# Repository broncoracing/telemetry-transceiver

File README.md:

# telemetry transceiver
Bronco racing BR24 telemetry transceiver.

Based on an XBee Pro 900HP transceiver, and an STM32F412 microcontroller with two CAN transceivers.

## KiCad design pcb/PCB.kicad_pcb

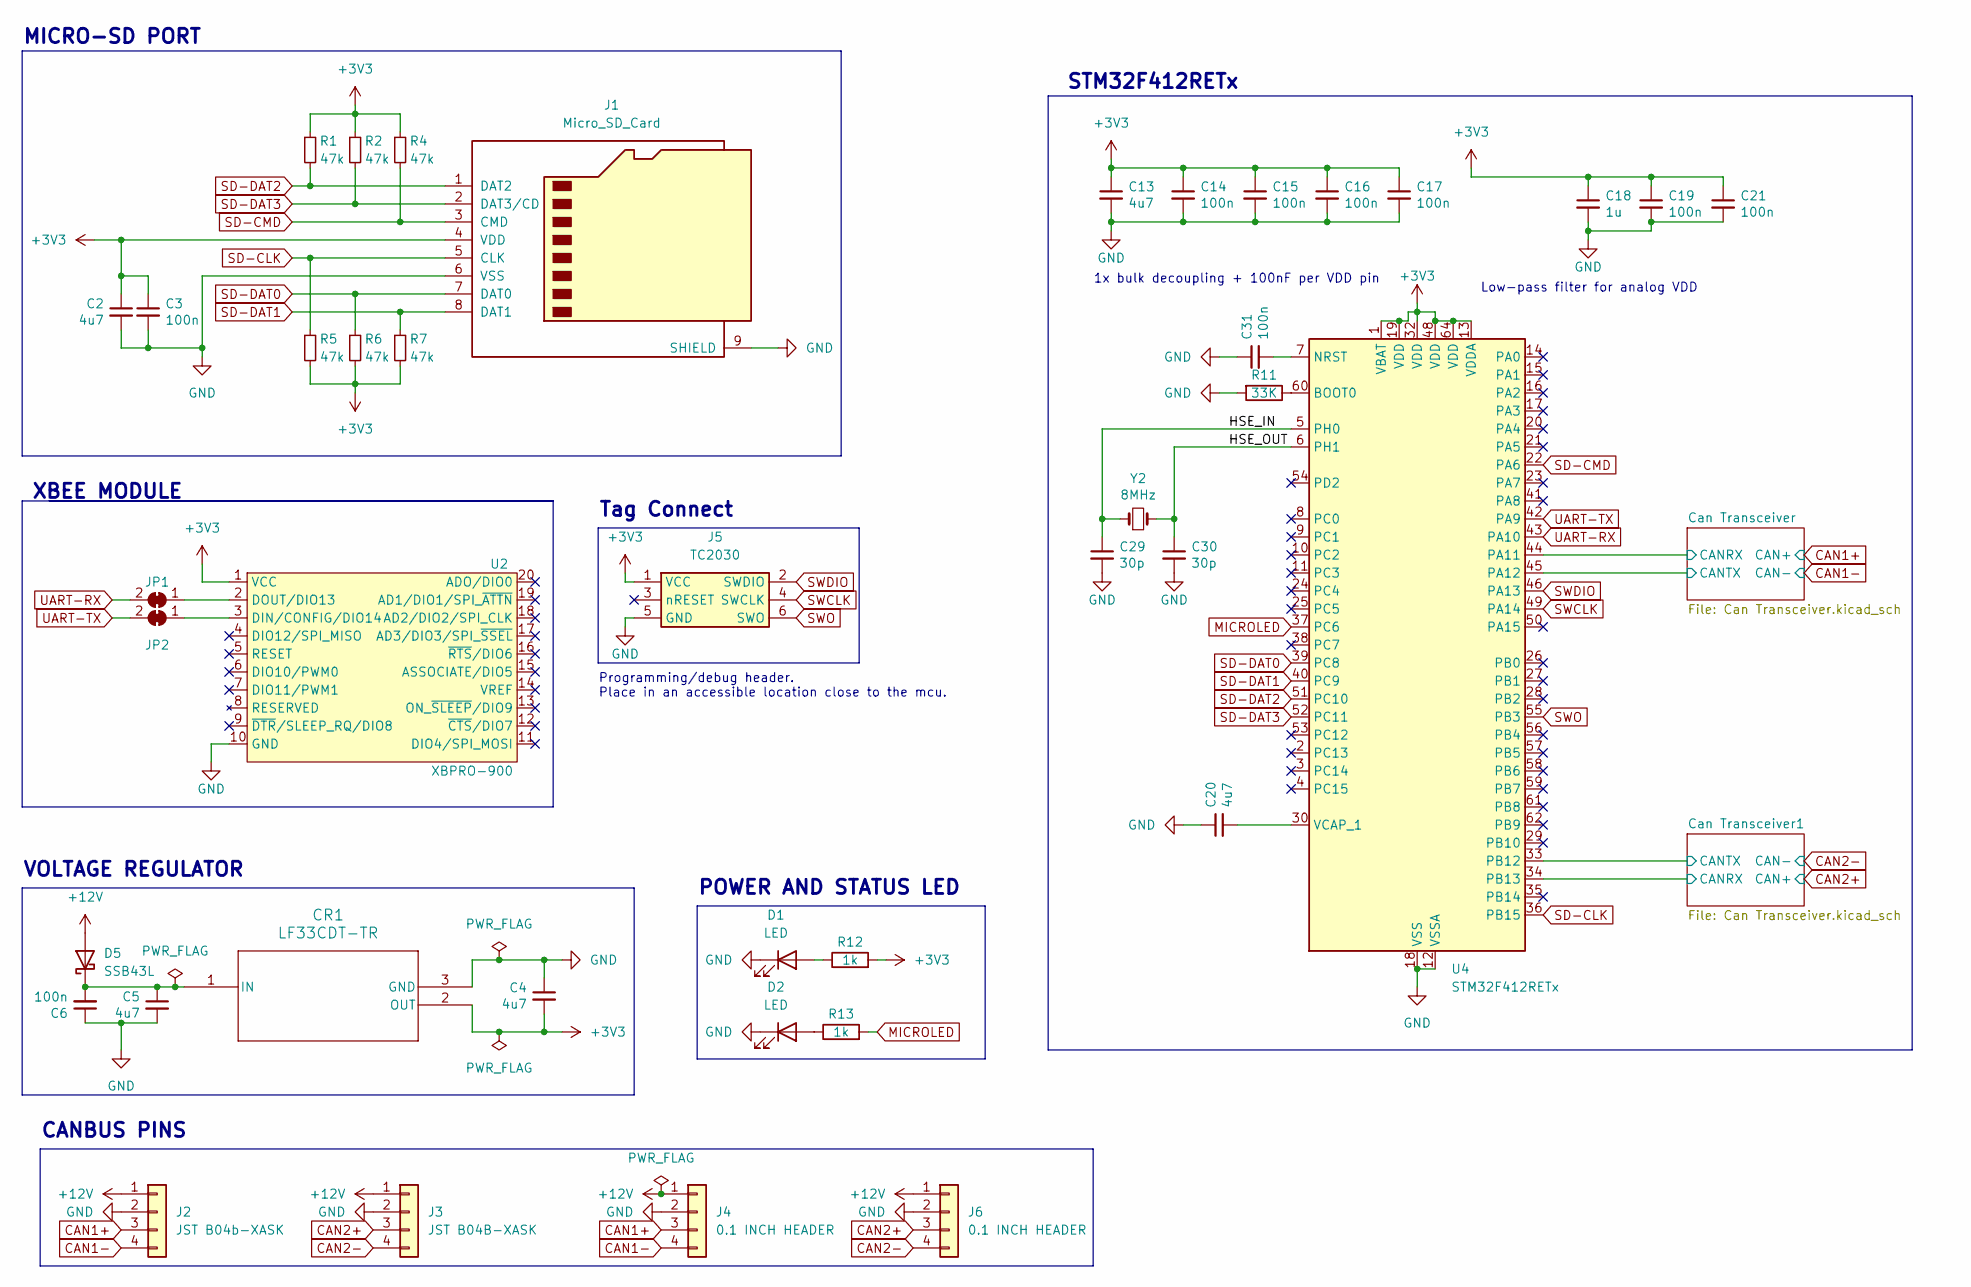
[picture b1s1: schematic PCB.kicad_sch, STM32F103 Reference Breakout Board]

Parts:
C2, C4, C5, C13, C20: 4u7; C_0603_1608Metric; LCSC C19666
C3, C6, C14, C15, C16, C17, C19, C21, C31: 100n; C_0603_1608Metric; LCSC C307331
C18: 1u; C_0603_1608Metric; LCSC C15849
C29, C30: 30p; C_0603_1608Metric; LCSC C1570
CR1: LF33CDT-TR; DPAK_STM
D1, D2: LED; LED_0603_1608Metric
D5: SSB43L; D_SMB
J1: Micro_SD_Card; microSD_HC_Wuerth_693072010801
J2: JST B04b-XASK; JST_XA_B04B-XASK-1_1x04_P2.50mm_Vertical
J3: JST B04B-XASK; JST_XA_B04B-XASK-1-A_1x04_P2.50mm_Vertical
J4, J6: 0.1 INCH HEADER; PinHeader_1x04_P2.54mm_Vertical
J5: TC2030; Tag-Connect_TC2030-IDC-NL_2x03_P1.27mm_Vertical
JP1, JP2: SolderJumper_2_Bridged; SolderJumper-2_P1.3mm_Bridged_RoundedPad1.0x1.5mm
R1, R2, R4, R5, R6, R7: 47k; R_0603_1608Metric
R11: 33K; R_0603_1608Metric
R12, R13: 1k; R_0603_1608Metric
U2: XBPRO-900; XBEEPRO900HP
U4: STM32F412RETx; LQFP-64_10x10mm_P0.5mm
Y2: 8MHz; Crystal_SMD_5032-2Pin_5.0x3.2mm; LCSC C115962

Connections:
+3V3: C2.1, C3.1, C4.2, C13.1, C14.1, C15.1, C16.1, C17.1, C18.1, C19.1, C21.1, CR1.2 (OUT), J1.4 (VDD), J5.1 (VCC), R1.1, R2.1, R4.1, R5.2, R6.2, R7.2, R12.2, U2.1 (VCC), U4.1 (VBAT), U4.13 (VDDA), U4.19 (VDD), U4.32 (VDD), U4.48 (VDD), U4.64 (VDD); also elsewhere on the board
+12V: D5.2 (A), J2.1, J3.1, J4.1, J6.1
/Can Transceiver1/CANRX: U4.34 (PB13); also elsewhere on the board
/Can Transceiver1/CANTX: U4.33 (PB12); also elsewhere on the board
/Can Transceiver/CANRX: U4.44 (PA11); also elsewhere on the board
/Can Transceiver/CANTX: U4.45 (PA12); also elsewhere on the board
/HSE_IN: C29.1, U4.5 (PH0), Y2.1
/HSE_OUT: C30.1, U4.6 (PH1), Y2.2
CAN1+: J2.3, J4.3; also elsewhere on the board
CAN1-: J2.4, J4.4; also elsewhere on the board
CAN2+: J3.3, J6.3; also elsewhere on the board
CAN2-: J3.4, J6.4; also elsewhere on the board
GND: C2.2, C3.2, C4.1, C5.2, C6.1, C13.2, C14.2, C15.2, C16.2, C17.2, C18.2, C19.2, C20.1, C21.2, C29.2, C30.2, C31.1, CR1.3 (GND), D1.1 (K), D2.1 (K), J1.6 (VSS), J1.9 (SHIELD), J2.2, J3.2, J4.2, J5.5 (GND), J6.2, R11.2, U2.10 (GND), U4.12 (VSSA), U4.18 (VSS), U4.31 (VSS), U4.47 (VSS), U4.63 (VSS); also elsewhere on the board
MICROLED: R13.2, U4.37 (PC6)
unnamed: C5.1, C6.2, CR1.1 (IN), D5.1 (K)
unnamed: D1.2 (A), R12.1
unnamed: D2.2 (A), R13.1
unnamed: JP1.1 (A), U2.2 (DOUT/DIO13)
unnamed: JP2.1 (A), U2.3 (DIN/CONFIG/DIO14)
unnamed: R11.1, U4.60 (BOOT0)
unnamed: C31.2, U4.7 (NRST)
unnamed: C20.2, U4.30 (VCAP_1)
SD-CLK: J1.5 (CLK), R5.1, U4.36 (PB15)
SD-CMD: J1.3 (CMD), R4.2, U4.22 (PA6)
SD-DAT0: J1.7 (DAT0), R6.1, U4.39 (PC8)
SD-DAT1: J1.8 (DAT1), R7.1, U4.40 (PC9)
SD-DAT2: J1.1 (DAT2), R1.2, U4.51 (PC10)
SD-DAT3: J1.2 (DAT3/CD), R2.2, U4.52 (PC11)
SWCLK: J5.4 (SWCLK), U4.49 (PA14)
SWDIO: J5.2 (SWDIO), U4.46 (PA13)
SWO: J5.6 (SWO), U4.55 (PB3)
UART-RX: JP1.2 (B), U4.43 (PA10)
UART-TX: JP2.2 (B), U4.42 (PA9)

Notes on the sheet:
STM32F412RETx
1x bulk decoupling + 100nF per VDD pin
Programming/debug header. Place in an accessible location close to the mcu.
VOLTAGE REGULATOR
XBEE MODULE
POWER AND STATUS LED
CANBUS PINS
MICRO-SD PORT
Tag Connect
Low-pass filter for analog VDD

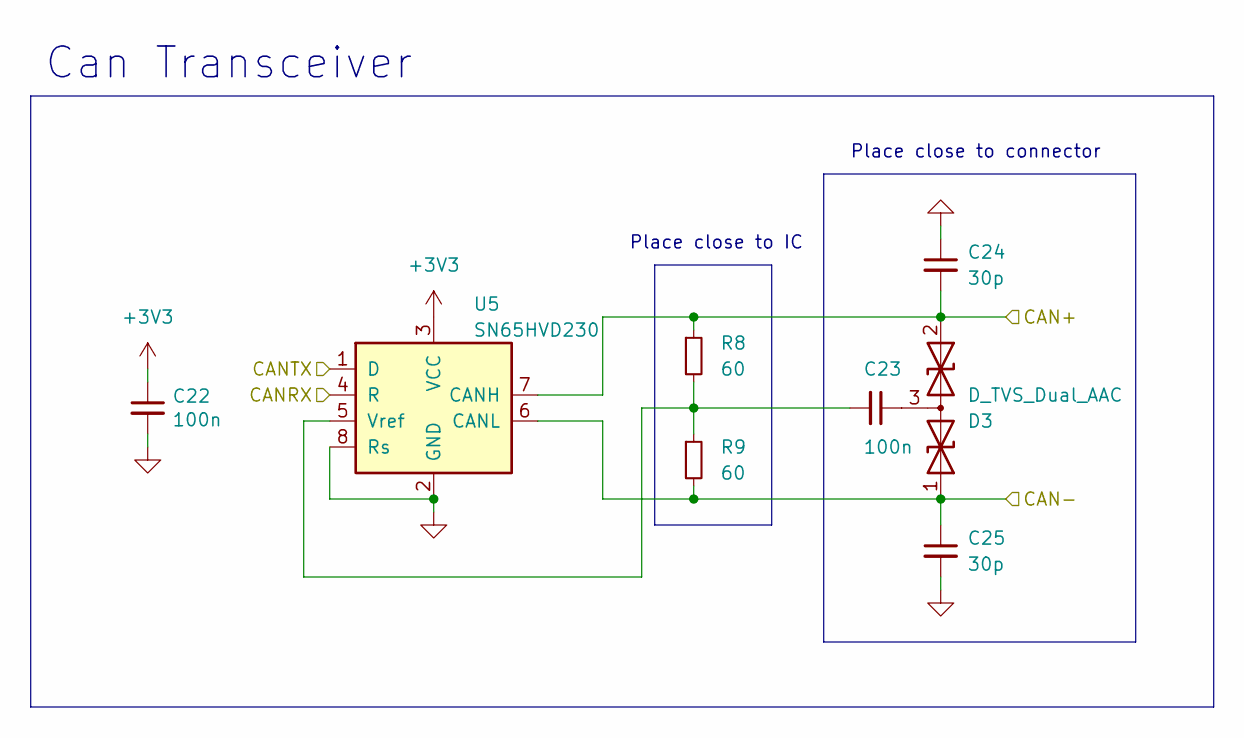
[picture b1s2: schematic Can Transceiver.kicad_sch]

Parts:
C22, C23: 100n; C_0603_1608Metric; LCSC C307331
C24, C25: 30p; C_0603_1608Metric; LCSC C1570
D3: D_TVS_Dual_AAC; SOT-323_SC-70; LCSC C151237
R8, R9: 60; R_0805_2012Metric; LCSC C441730
U5: SN65HVD230; SOIC-8_3.9x4.9mm_P1.27mm; LCSC C12084

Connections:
+3V3: C22.1, U5.3 (VCC); also elsewhere on the board
/Can Transceiver/CANRX: U5.4 (R); also elsewhere on the board
/Can Transceiver/CANTX: U5.1 (D); also elsewhere on the board
CAN1+: C24.2, D3.2 (A2), R8.1, U5.7 (CANH); also elsewhere on the board
CAN1-: C25.1, D3.1 (A1), R9.2, U5.6 (CANL); also elsewhere on the board
GND: C22.2, C24.1, C25.2, U5.2 (GND), U5.8 (Rs); also elsewhere on the board
unnamed: C23.1, D3.3 (common)
unnamed: C23.2, R8.2, R9.1, U5.5 (Vref)

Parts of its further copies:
C1, C26: 100n; C_0603_1608Metric; LCSC C307331
C27, C28: 30p; C_0603_1608Metric; LCSC C1570
D4: D_TVS_Dual_AAC; SOT-323_SC-70; LCSC C151237
R3, R10: 60; R_0805_2012Metric; LCSC C441730
U1: SN65HVD230; SOIC-8_3.9x4.9mm_P1.27mm; LCSC C12084

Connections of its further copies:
+3V3: C1.1, U1.3 (VCC); also elsewhere on the board
/Can Transceiver1/CANRX: U1.4 (R); also elsewhere on the board
/Can Transceiver1/CANTX: U1.1 (D); also elsewhere on the board
CAN2+: C27.2, D4.2 (A2), R3.1, U1.7 (CANH); also elsewhere on the board
CAN2-: C28.1, D4.1 (A1), R10.2, U1.6 (CANL); also elsewhere on the board
GND: C1.2, C27.1, C28.2, U1.2 (GND), U1.8 (Rs); also elsewhere on the board
unnamed: C26.1, D4.3 (common)
unnamed: C26.2, R3.2, R10.1, U1.5 (Vref)

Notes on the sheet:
Can Transceiver
Place close to connector
Place close to IC

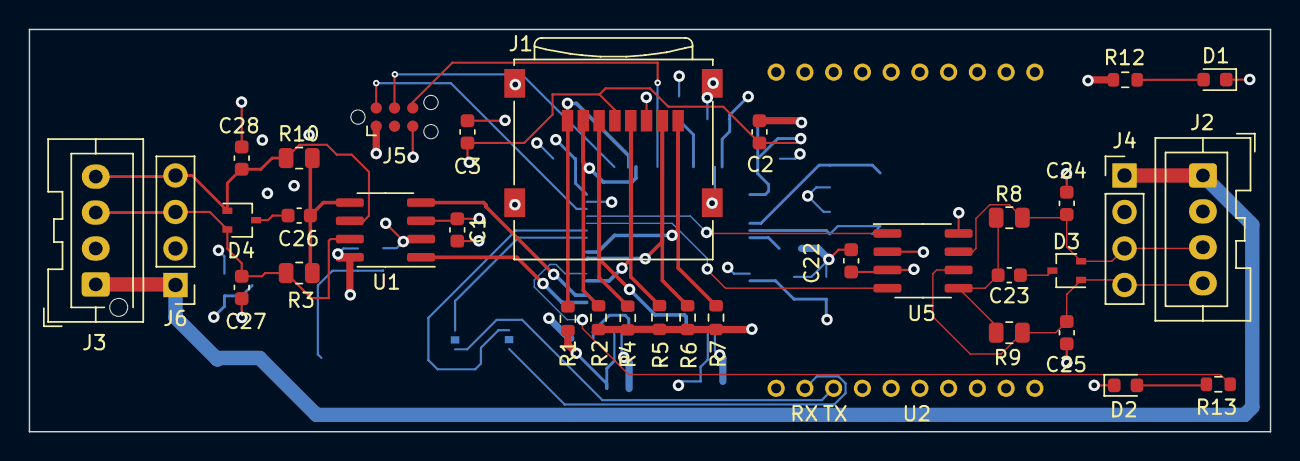
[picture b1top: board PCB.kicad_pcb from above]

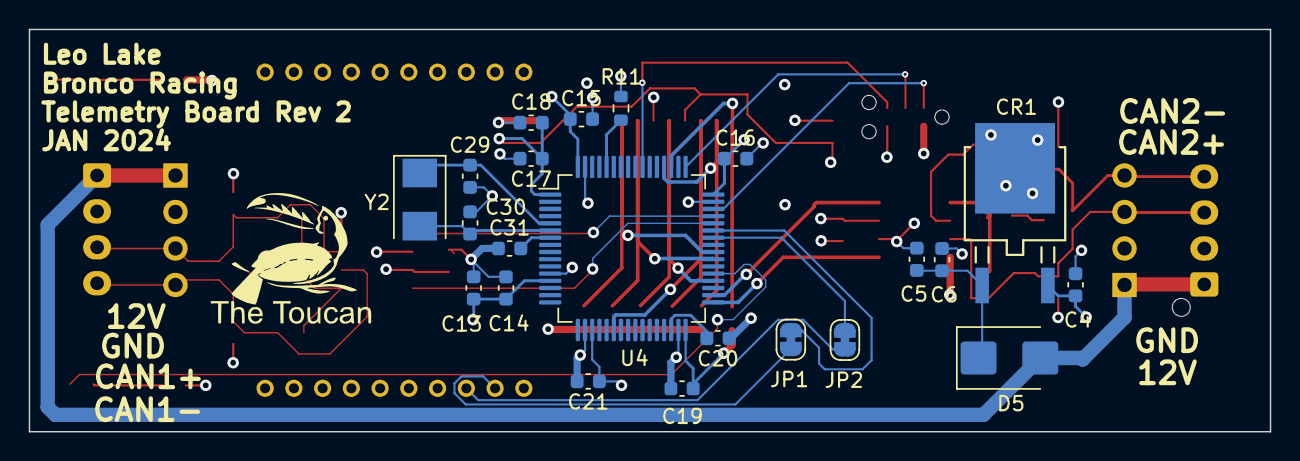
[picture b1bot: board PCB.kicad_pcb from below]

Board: 4 copper layers, 86.4 x 28.0 mm, 57 parts (22 on the bottom side), 37 nets.

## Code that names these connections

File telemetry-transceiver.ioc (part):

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Mcu.Name=STM32F412R(E-G)Tx
Mcu.Package=LQFP64
Mcu.UserName=STM32F412RETx
PA10.Mode=Asynchronous
PA10.Signal=USART1_RX
PA11.Mode=CAN_Activate
PA11.Signal=CAN1_RX
PA12.Mode=CAN_Activate
PA12.Signal=CAN1_TX
PA13.Mode=Trace_Asynchronous_SW
PA13.Signal=SYS_JTMS-SWDIO
PA14.Mode=Trace_Asynchronous_SW
PA14.Signal=SYS_JTCK-SWCLK
PA6.Mode=SD_4_bits_Wide_bus
PA6.Signal=SDIO_CMD
PA9.Mode=Asynchronous
PA9.Signal=USART1_TX
PB12.Mode=CAN_Activate
PB12.Signal=CAN2_RX
PB13.Mode=CAN_Activate
PB13.Signal=CAN2_TX
PB15.Mode=SD_4_bits_Wide_bus
PB15.Signal=SDIO_CK
PB3.Mode=Trace_Asynchronous_SW
PB3.Signal=SYS_JTDO-SWO
PC10.Mode=SD_4_bits_Wide_bus
PC10.Signal=SDIO_D2
PC11.Mode=SD_4_bits_Wide_bus
PC11.Signal=SDIO_D3
PC8.Mode=SD_4_bits_Wide_bus
PC8.Signal=SDIO_D0
PC9.Mode=SD_4_bits_Wide_bus
PC9.Signal=SDIO_D1
PH0\ -\ OSC_IN.Mode=HSE-External-Oscillator
PH0\ -\ OSC_IN.Signal=RCC_OSC_IN
PH1\ -\ OSC_OUT.Mode=HSE-External-Oscillator
PH1\ -\ OSC_OUT.Signal=RCC_OSC_OUT
RCC.SYSCLKFreq_VALUE=80000000
RCC.SYSCLKSource=RCC_SYSCLKSOURCE_PLLCLK
board=custom

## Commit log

2023-10-13 Removed Kicad Library folder
2023-10-27 created schematic and layout of the telemetry board
2024-02-01 Finished Telemetry PCB
2024-03-23 created firmware project:
